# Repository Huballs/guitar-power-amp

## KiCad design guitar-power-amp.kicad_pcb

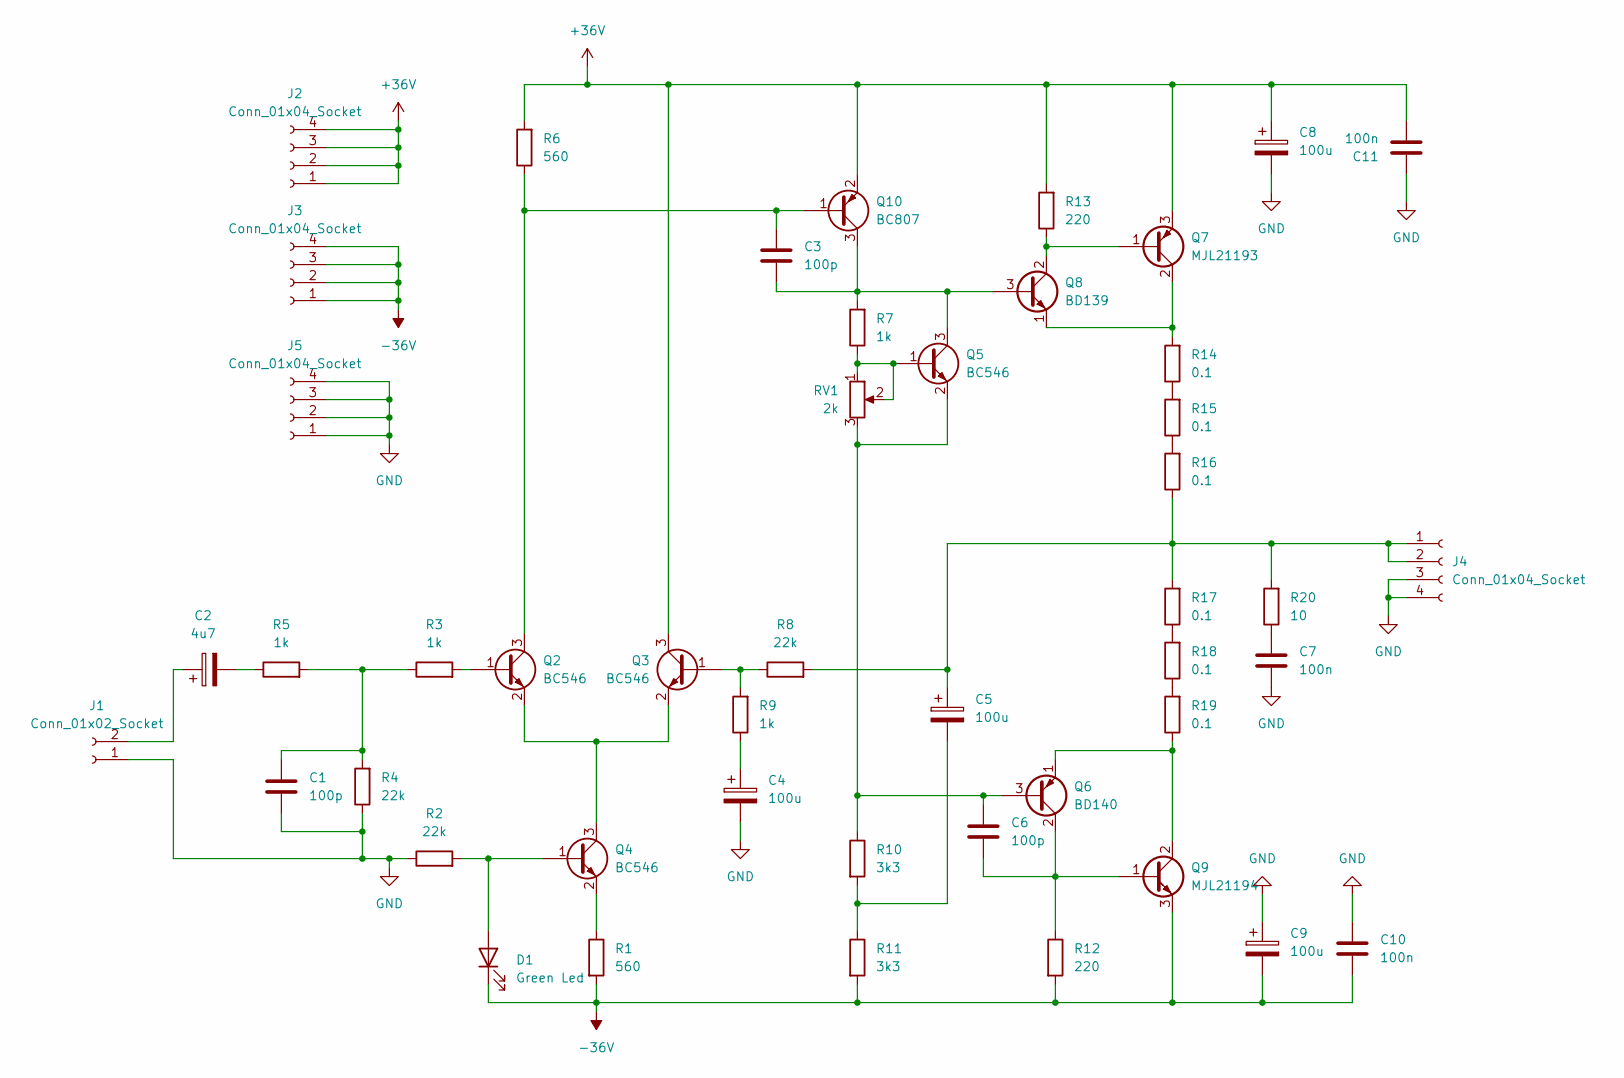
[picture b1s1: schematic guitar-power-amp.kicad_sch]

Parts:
C1, C3, C6: 100p; C_Rect_L7.0mm_W6.0mm_P5.00mm
C2: 4u7; CP_Radial_D5.0mm_P2.50mm
C4, C5, C8, C9: 100u; CP_Radial_D8.0mm_P3.50mm
C7: 100n; C_Rect_L7.0mm_W2.5mm_P5.00mm
C10, C11: 100n; C_0805_2012Metric_Pad1.18x1.45mm_HandSolder
D1: Green Led; LED_D3.0mm
J1: Conn_01x02_Socket; PinHeader_1x02_P2.54mm_Vertical
J2, J3, J4, J5: Conn_01x04_Socket; PinHeader_1x04_P2.54mm_Vertical
Q2, Q3, Q4, Q5: BC546; SOT-23
Q6: BD140; TO-126-3_Vertical
Q7: MJL21193; TO-247-3_Horizontal_TabDown
Q8: BD139; TO-126-3_Vertical
Q9: MJL21194; TO-247-3_Horizontal_TabDown
Q10: BC807; SOT-23
R1, R6: 560; R_1206_3216Metric_Pad1.30x1.75mm_HandSolder
R2, R4, R8: 22k; R_1206_3216Metric_Pad1.30x1.75mm_HandSolder
R3, R5, R7, R9: 1k; R_1206_3216Metric_Pad1.30x1.75mm_HandSolder
R10, R11: 3k3; R_1206_3216Metric_Pad1.30x1.75mm_HandSolder
R12, R13: 220; R_1206_3216Metric_Pad1.30x1.75mm_HandSolder
R14, R15, R16, R17, R18, R19: 0.1; R_2512_6332Metric_Pad1.40x3.35mm_HandSolder
R20: 10; R_2512_6332Metric_Pad1.40x3.35mm_HandSolder
RV1: 2k; Potentiometer_Bourns_3266Y_Vertical

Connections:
+36V: C8.1, C11.2, J2.1, J2.2, J2.3, J2.4, Q3.3 (C), Q7.3 (E), Q10.2 (E), R6.2, R13.2
-36V: C9.2, C10.2, D1.1 (K), J3.1, J3.2, J3.3, J3.4, Q9.3 (E), R1.2, R11.2, R12.2
GND: C1.2, C4.2, C7.2, C8.2, C9.1, C10.1, C11.1, J1.1, J4.3, J4.4, J5.1, J5.2, J5.3, J5.4, R2.1, R4.1
unnamed: C1.1, R3.1, R4.2, R5.2
unnamed: C2.2, R5.1
unnamed: C4.1, R9.1
unnamed: C5.2, R10.2, R11.1
unnamed: C7.1, R20.1
unnamed: D1.2 (A), Q4.1 (B), R2.2
unnamed: C2.1, J1.2
unnamed: C5.1, J4.1, J4.2, R8.2, R16.1, R17.2, R20.2
unnamed: Q2.1 (B), R3.2
unnamed: Q2.2 (E), Q3.2 (E), Q4.3 (C)
unnamed: Q3.1 (B), R8.1, R9.2
unnamed: Q4.2 (E), R1.1
unnamed: Q5.1 (B), R7.1, RV1.1, RV1.2
unnamed: C6.1, Q5.2 (E), Q6.3 (B), R10.1, RV1.3
unnamed: C6.2, Q6.2 (C), Q9.1 (B), R12.1
unnamed: Q6.1 (E), Q9.2 (C), R19.1
unnamed: Q7.1 (B), Q8.2 (C), R13.1
unnamed: Q7.2 (C), Q8.1 (E), R14.2
unnamed: C3.1, Q2.3 (C), Q10.1 (B), R6.1
unnamed: C3.2, Q5.3 (C), Q8.3 (B), Q10.3 (C), R7.2
unnamed: R14.1, R15.2
unnamed: R15.1, R16.2
unnamed: R17.1, R18.2
unnamed: R18.1, R19.2

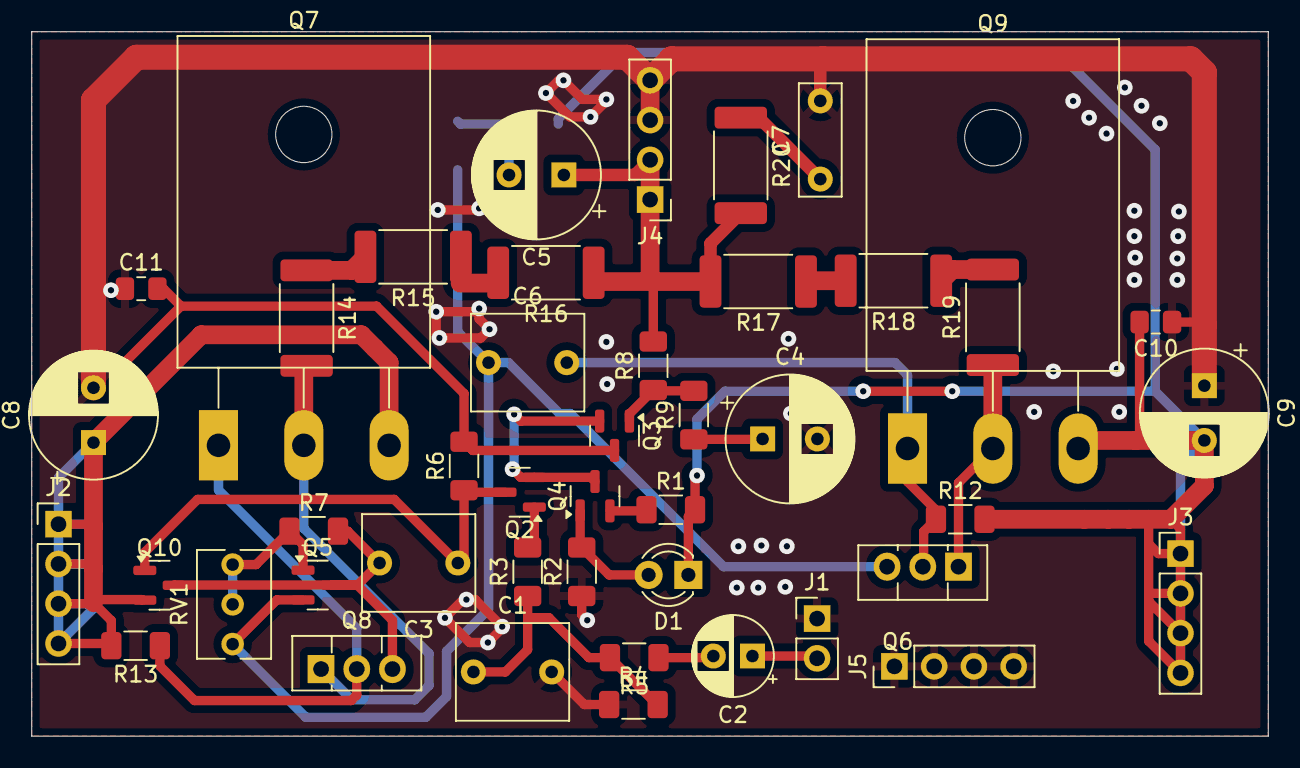
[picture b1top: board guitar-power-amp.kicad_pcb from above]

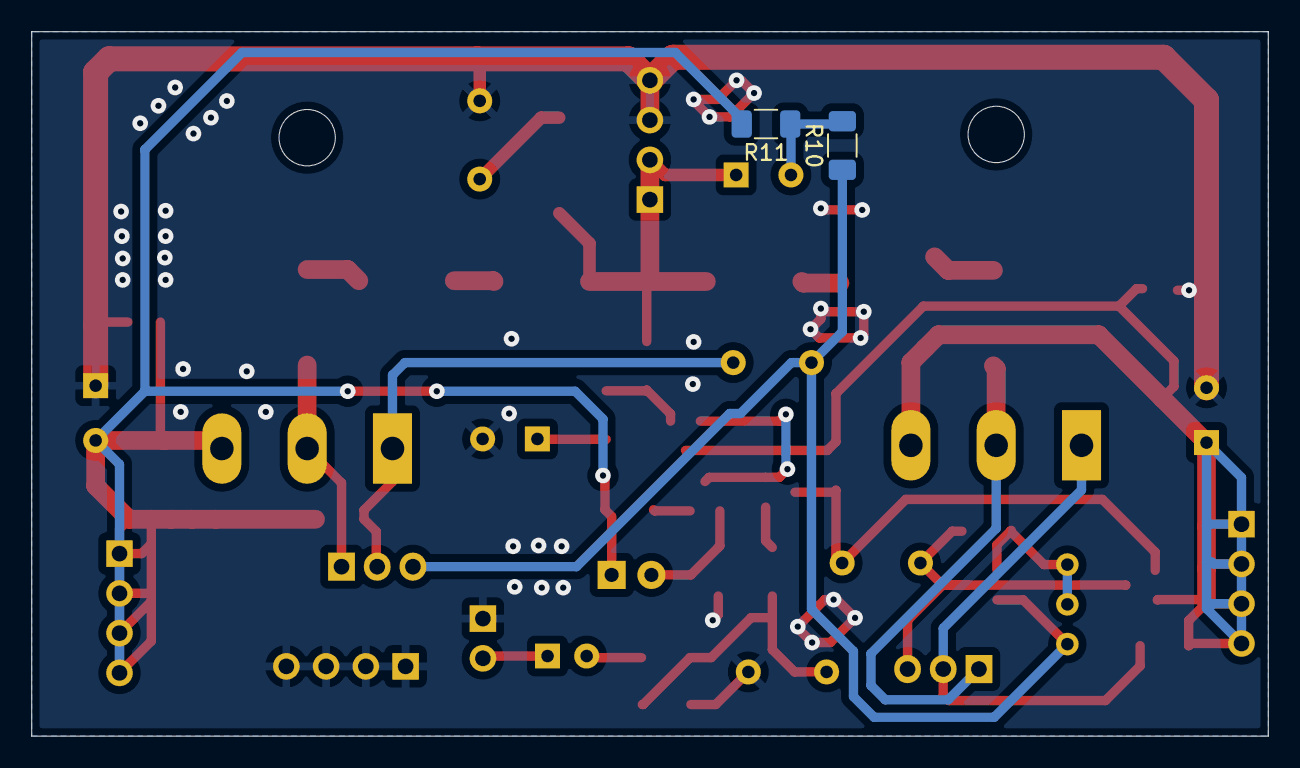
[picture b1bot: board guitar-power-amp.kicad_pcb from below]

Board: 2 copper layers, 79.0 x 45.0 mm, 47 parts (2 on the bottom side), 27 nets.

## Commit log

2025-01-31 init
